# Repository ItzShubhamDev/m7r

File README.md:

# M7R
A 7 Keys Macropad with a Rotary Encoder and a 0.91 inch OLED Display powered by SeeedStudio XIAO RP2040

## Features
- Utility Shortcuts
- Per Key RGB
- Multiple Layers
- OLED Display

## Bill of Materials

|       Name       |      Footprint      |  Quantity  |
|------------------|---------------------|------------|
|     MX Switch    |     MX_PCB_1.00u    |      7     |
|       Diode      |     Diode_DO-35     |      8     |
|  Rotary Encoder  |   Encoder_EC11_MX   |      1     |
|   OLED Display   |     OLED_128x32     |      1     |
|        LED       |    LED_SK6812MINI   |      7     |
|  XIAO RP2040 MCU |  Seeed_XIAO_RP2040  |      1     |
|        PCB       |          -          |      1     |
|   Printed Case   |          -          |      1     |

## Images

### Schematic

### PCB (Front)

### PCB (Back)

### PCB (3D Front)

### PCB (3D Back)

### Case

## Additional Information

- **Firmware**: [KMK](https://github.com/KMKfw/kmk_firmware/)
- **Symbols and FootPrints**: [ScottoKicad](https://github.com/joe-scotto/scottokeebs/tree/main/Extras/ScottoKicad)
- **PCB Software**: [Kicad](https://www.kicad.org/)
- **3D Design Software**: [Autodesk Fusion 360](https://www.autodesk.com/in/products/fusion-360/overview)

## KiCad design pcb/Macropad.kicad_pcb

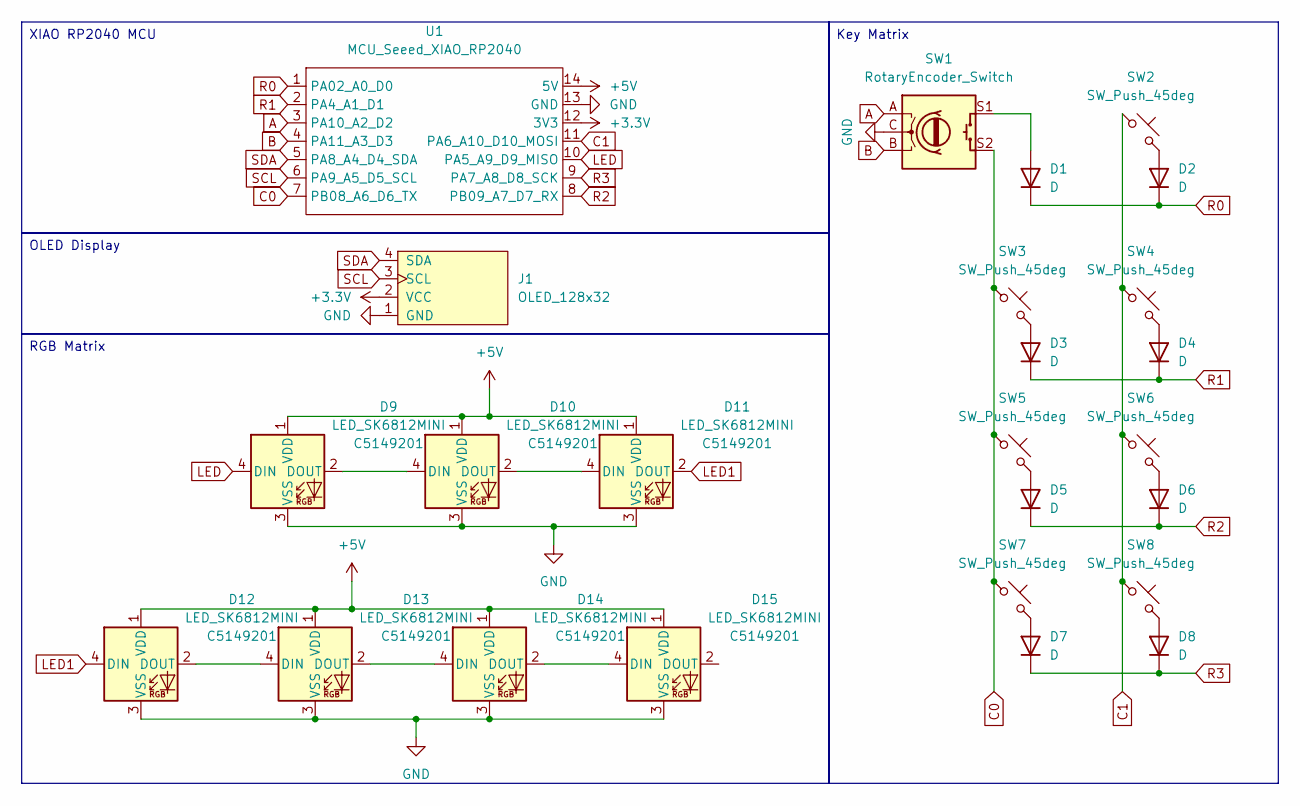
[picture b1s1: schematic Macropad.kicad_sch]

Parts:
D1, D2, D3, D4, D5, D6, D7, D8: D; Diode_DO-35
D9, D10, D11, D12, D13, D14, D15: LED_SK6812MINI; LCSC C5149201
J1: OLED_128x32
SW1: RotaryEncoder_Switch; Encoder_EC11_MX
SW2, SW3, SW4, SW5, SW6, SW7, SW8: SW_Push_45deg; MX_PCB_1.00u
U1: MCU_Seeed_XIAO_RP2040; Seeed_XIAO_RP2040

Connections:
+3.3V: J1.2 (VCC), U1.12 (3V3)
+5V: D9.1 (VDD), D10.1 (VDD), D11.1 (VDD), D12.1 (VDD), D13.1 (VDD), D14.1 (VDD), D15.1 (VDD), U1.14 (5V)
A: SW1.A, U1.3 (PA10_A2_D2)
B: SW1.B, U1.4 (PA11_A3_D3)
C0: SW1.S2, SW3.1, SW5.1, SW7.1, U1.7 (PB08_A6_D6_TX)
C1: SW2.1, SW4.1, SW6.1, SW8.1, U1.11 (PA6_A10_D10_MOSI)
GND: D9.3 (VSS), D10.3 (VSS), D11.3 (VSS), D12.3 (VSS), D13.3 (VSS), D14.3 (VSS), D15.3 (VSS), J1.1 (GND), SW1.C, U1.13 (GND)
LED: D9.4 (DIN), U1.10 (PA5_A9_D9_MISO)
LED1: D11.2 (DOUT), D12.4 (DIN)
unnamed: D1.2 (A), SW1.S1
unnamed: D2.2 (A), SW2.2
unnamed: D3.2 (A), SW3.2
unnamed: D4.2 (A), SW4.2
unnamed: D5.2 (A), SW5.2
unnamed: D6.2 (A), SW6.2
unnamed: D7.2 (A), SW7.2
unnamed: D8.2 (A), SW8.2
unnamed: D9.2 (DOUT), D10.4 (DIN)
unnamed: D10.2 (DOUT), D11.4 (DIN)
unnamed: D12.2 (DOUT), D13.4 (DIN)
unnamed: D13.2 (DOUT), D14.4 (DIN)
unnamed: D14.2 (DOUT), D15.4 (DIN)
R0: D1.1 (K), D2.1 (K), U1.1 (PA02_A0_D0)
R1: D3.1 (K), D4.1 (K), U1.2 (PA4_A1_D1)
R2: D5.1 (K), D6.1 (K), U1.8 (PB09_A7_D7_RX)
R3: D7.1 (K), D8.1 (K), U1.9 (PA7_A8_D8_SCK)
SCL: J1.3 (SCL), U1.6 (PA9_A5_D5_SCL)
SDA: J1.4 (SDA), U1.5 (PA8_A4_D4_SDA)

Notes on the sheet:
OLED Display
XIAO RP2040 MCU
RGB Matrix
Key Matrix

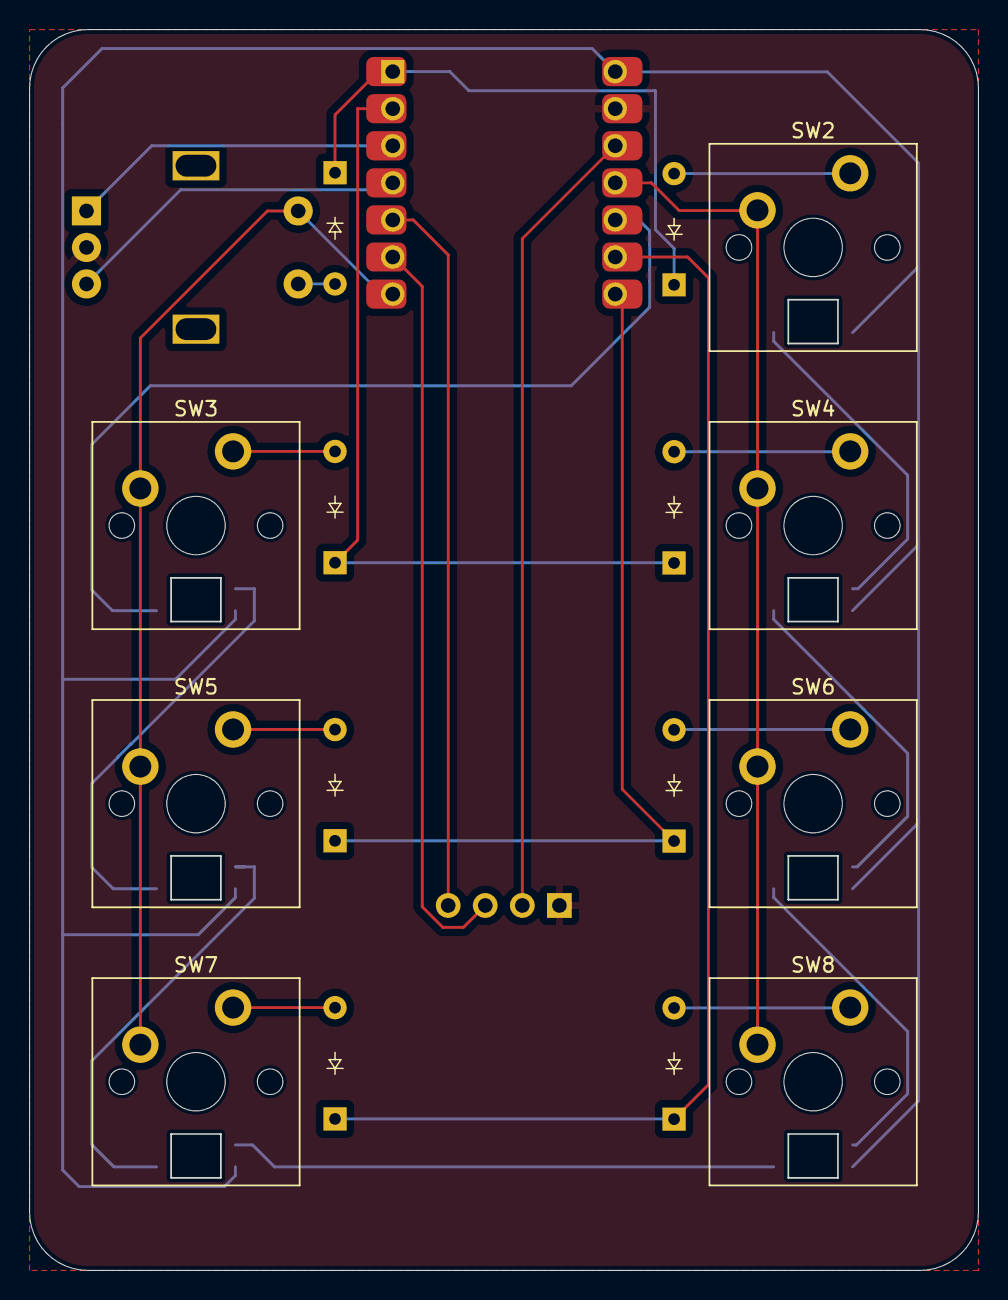
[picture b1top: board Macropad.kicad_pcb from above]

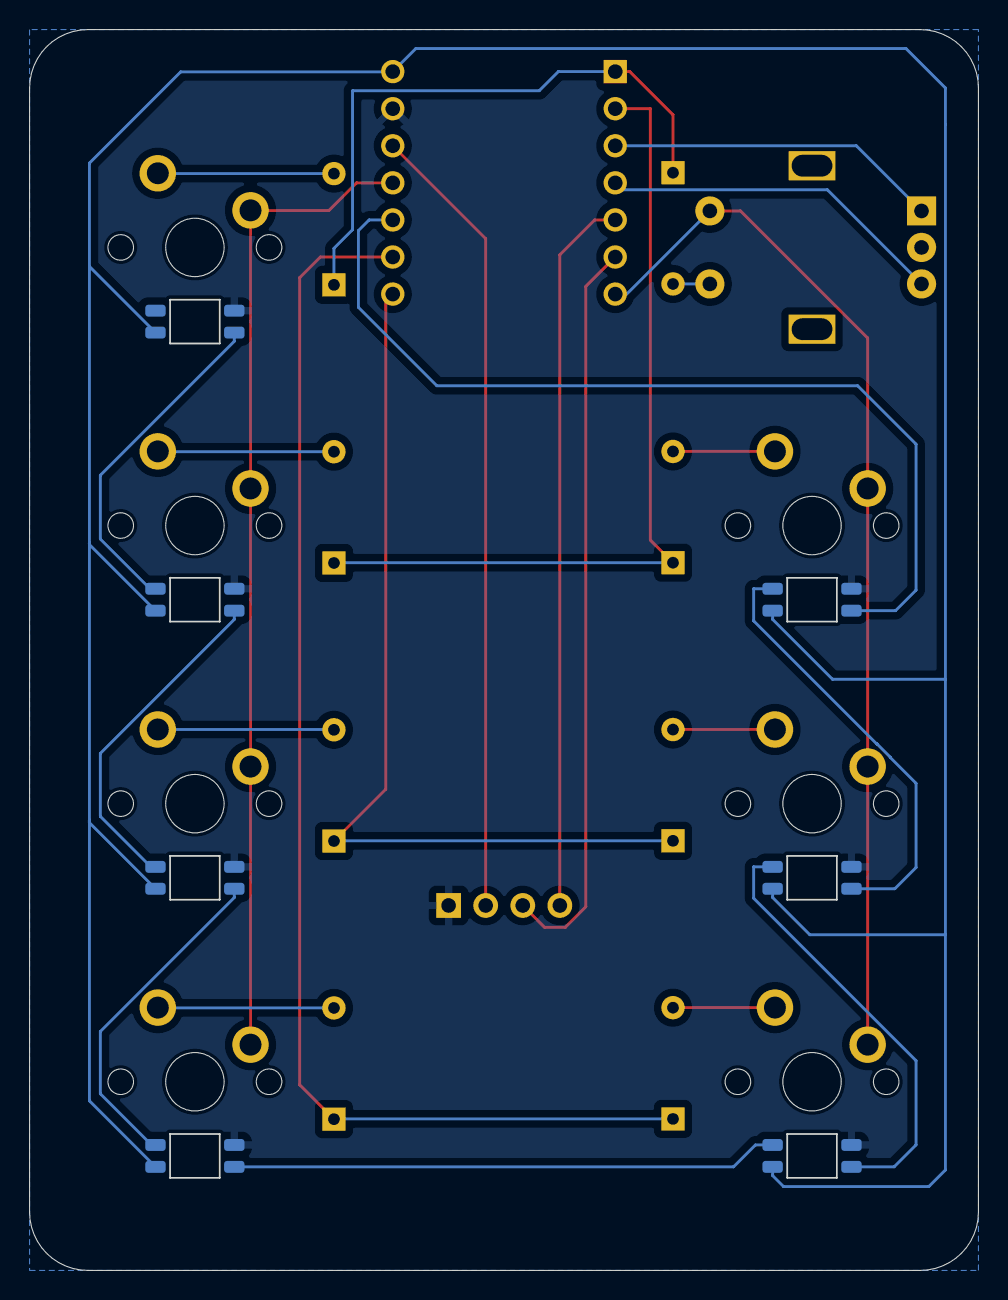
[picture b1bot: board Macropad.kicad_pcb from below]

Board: 2 copper layers, 64.9 x 84.9 mm, 25 parts (7 on the bottom side), 28 nets.

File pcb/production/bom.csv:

Designator,Footprint,Quantity,Value,LCSC Part #
"D1, D2, D3, D4, D5, D6, D7, D8",Diode_DO-35,8,D,
"D10, D11, D12, D13, D14, D15, D9",LED_SK6812MINI,7,LED_SK6812MINI,C5149201
J1,OLED_128x32,1,OLED_128x32,
SW1,Encoder_EC11_MX,1,RotaryEncoder_Switch,
"SW2, SW3, SW4, SW5, SW6, SW7, SW8",MX_PCB_1.00u,7,SW_Push_45deg,
U1,Seeed_XIAO_RP2040,1,MCU_Seeed_XIAO_RP2040,

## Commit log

2025-08-01 Reorganise files
2025-08-02 Fix Rotary Encoder
